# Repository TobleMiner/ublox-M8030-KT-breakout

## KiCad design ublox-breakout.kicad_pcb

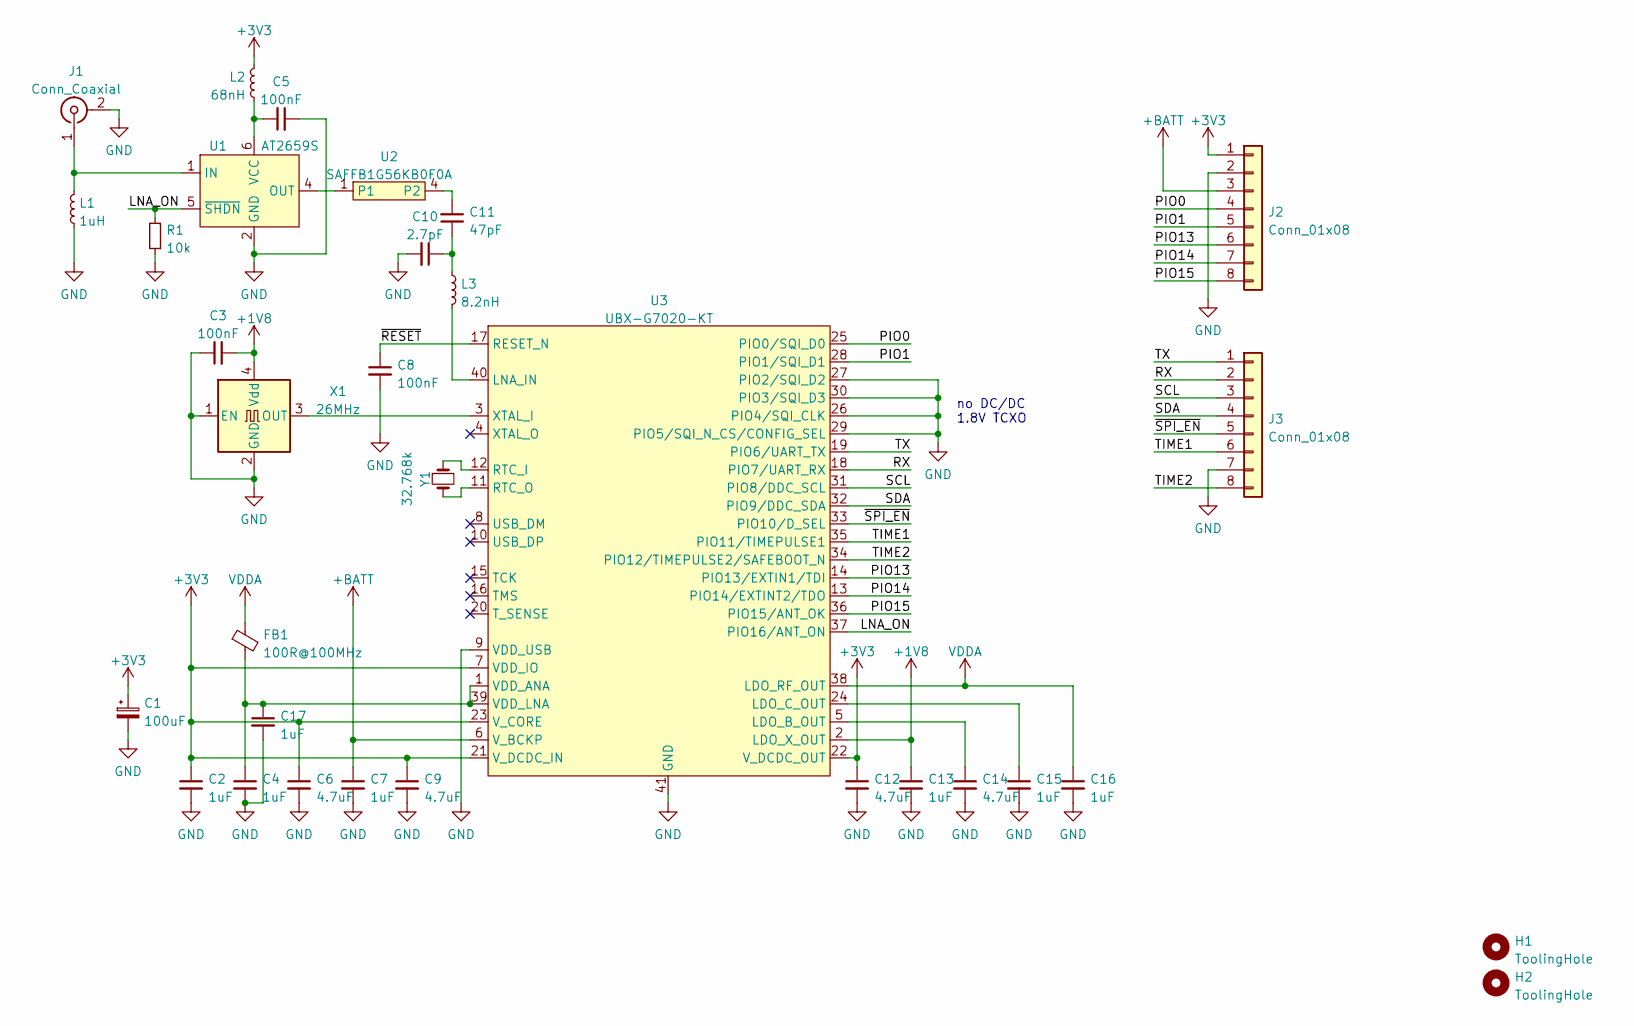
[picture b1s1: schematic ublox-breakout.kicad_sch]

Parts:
C1: 100uF; CP_EIA-3528-21_Kemet-B; LCSC C16133
C2, C4, C7, C13, C15, C16, C17: 1uF; C_0402_1005Metric; LCSC C52923
C3, C5, C8: 100nF; C_0402_1005Metric; LCSC C1525
C6, C9, C12, C14: 4.7uF; C_0402_1005Metric; LCSC C23733
C10: 2.7pF; C_0402_1005Metric; LCSC C1561
C11: 47pF; C_0402_1005Metric; LCSC C1567
FB1: 100R@100MHz; L_0402_1005Metric; LCSC C76891
H1, H2: ToolingHole; ToolingHole_JLCSMT
J1: Conn_Coaxial; SMA_Samtec_SMA-J-P-X-ST-EM1_EdgeMount; LCSC C2913580
J2, J3: Conn_01x08; PinHeader_1x08_P2.54mm_Vertical
L1: 1uH; L_0603_1608Metric; LCSC C275338
L2: 68nH; L_0603_1608Metric; LCSC C13415
L3: 8.2nH; L_0402_1005Metric; LCSC C84404
R1: 10k; R_0402_1005Metric; LCSC C25744
U1: AT2659S; SOT-23-6; LCSC C883443
U2: SAFFB1G56KB0F0A; Murata_LGA-5; LCSC C91647
U3: UBX-G7020-KT; QFN-40-1EP_5x5mm_P0.4mm_EP3.6x3.6mm
X1: 26MHz; Crystal_SMD_3225-4Pin_3.2x2.5mm; LCSC C213404
Y1: 32.768k; Crystal_SMD_3215-2Pin_3.2x1.5mm; LCSC C32346

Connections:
+1V8: C3.2, C13.1, U3.2 (LDO_X_OUT), X1.4 (Vdd)
+3V3: C1.1, C2.1, C6.1, C9.1, C12.1, J2.1, L2.1, U3.7 (VDD_IO), U3.21 (V_DCDC_IN), U3.22 (V_DCDC_OUT), U3.23 (V_CORE)
+BATT: C7.1, J2.3, U3.6 (V_BCKP)
/LNA_ON: R1.2, U1.5 (~SHDN), U3.37 (PIO16/ANT_ON)
/PIO0: J2.4, U3.25 (PIO0/SQI_D0)
/PIO1: J2.5, U3.28 (PIO1/SQI_D1)
/PIO13: J2.6, U3.14 (PIO13/EXTIN1/TDI)
/PIO14: J2.7, U3.13 (PIO14/EXTINT2/TDO)
/PIO15: J2.8, U3.36 (PIO15/ANT_OK)
/RX: J3.2, U3.18 (PIO7/UART_RX)
/SCL: J3.3, U3.31 (PIO8/DDC_SCL)
/SDA: J3.4, U3.32 (PIO9/DDC_SDA)
/TIME1: J3.6, U3.35 (PIO11/TIMEPULSE1)
/TIME2: J3.8, U3.34 (PIO12/TIMEPULSE2/SAFEBOOT_N)
/TX: J3.1, U3.19 (PIO6/UART_TX)
/~RESET: C8.1, U3.17 (RESET_N)
/~SPI_EN: J3.5, U3.33 (PIO10/D_SEL)
GND: C1.2, C2.2, C3.1, C4.2, C5.2, C6.2, C7.2, C8.2, C9.2, C10.2, C12.2, C13.2, C14.2, C15.2, C16.2, C17.2, J1.2 (Ext), J2.2, J3.7, L1.1, R1.1, U1.2 (GND), U1.3 (GND), U2.2, U2.3, U2.5, U3.9 (VDD_USB), U3.26 (PIO4/SQI_CLK), U3.27 (PIO2/SQI_D2), U3.29 (PIO5/SQI_N_CS/CONFIG_SEL), U3.30 (PIO3/SQI_D3), U3.41 (GND), X1.1 (EN), X1.2 (GND)
unnamed: C4.1, C17.1, FB1.2, U3.1 (VDD_ANA), U3.39 (VDD_LNA)
unnamed: C5.1, L2.2, U1.6 (VCC)
unnamed: C10.1, C11.1, L3.1
unnamed: C11.2, U2.4 (P2)
unnamed: C14.1, U3.5 (LDO_B_OUT)
unnamed: C15.1, U3.24 (LDO_C_OUT)
unnamed: J1.1 (In), L1.2, U1.1 (IN)
unnamed: L3.2, U3.40 (LNA_IN)
unnamed: U1.4 (OUT), U2.1
unnamed: U3.3 (XTAL_I), X1.3 (OUT)
unnamed: U3.11 (RTC_O), Y1.2
unnamed: U3.12 (RTC_I), Y1.1
VDDA: C16.1, FB1.1, U3.38 (LDO_RF_OUT)

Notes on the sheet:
no DC/DC 1.8V TCXO

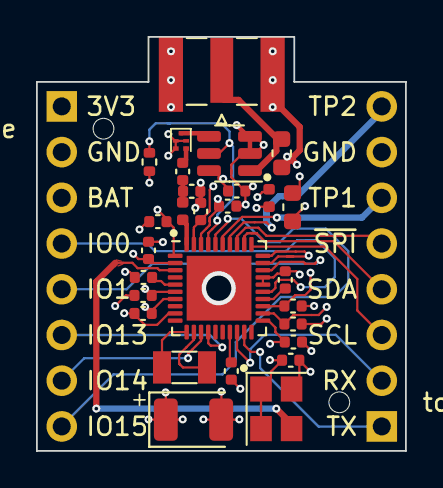
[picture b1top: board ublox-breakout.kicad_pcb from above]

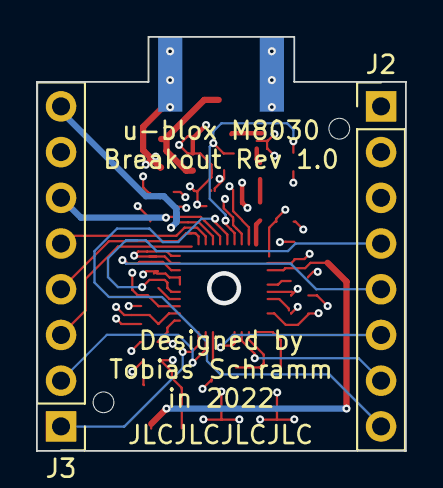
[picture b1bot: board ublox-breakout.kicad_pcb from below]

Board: 4 copper layers, 20.5 x 23.0 mm, 32 parts (2 on the bottom side), 31 nets.

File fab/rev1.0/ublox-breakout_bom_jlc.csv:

"Comment","Designator","Footprint","LCSC Part #"
"100uF","C1","CP_EIA-3528-21_Kemet-B","C16133"
"1uF","C2,C4,C7,C13,C15,C16,C17","C_0402_1005Metric","C52923"
"100nF","C3,C5,C8","C_0402_1005Metric","C1525"
"4.7uF","C6,C9,C12,C14","C_0402_1005Metric","C23733"
"2.7pF","C10","C_0402_1005Metric","C1561"
"47pF","C11","C_0402_1005Metric","C1567"
"100R@100MHz","FB1","L_0402_1005Metric","C76891"
"Conn_Coaxial","J1","SMA_Samtec_SMA-J-P-X-ST-EM1_EdgeMount","C2913580"
"1uH","L1","L_0603_1608Metric","C275338"
"68nH","L2","L_0603_1608Metric","C13415"
"8.2nH","L3","L_0402_1005Metric","C84404"
"10k","R1","R_0402_1005Metric","C25744"
"AT2659S","U1","SOT-23-6","C883443"
"SAFFB1G56KB0F0A","U2","Murata_LGA-5","C91647"
"26MHz","X1","Crystal_SMD_3225-4Pin_3.2x2.5mm","C213404"
"32.768k","Y1","Crystal_SMD_3215-2Pin_3.2x1.5mm","C32346"

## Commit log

2022-06-06 Add JLCSMT tooling hole library
2022-06-06 Finish layout
2024-12-21 Create Jun
